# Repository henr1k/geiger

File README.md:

# geiger

Simple Geiger counter

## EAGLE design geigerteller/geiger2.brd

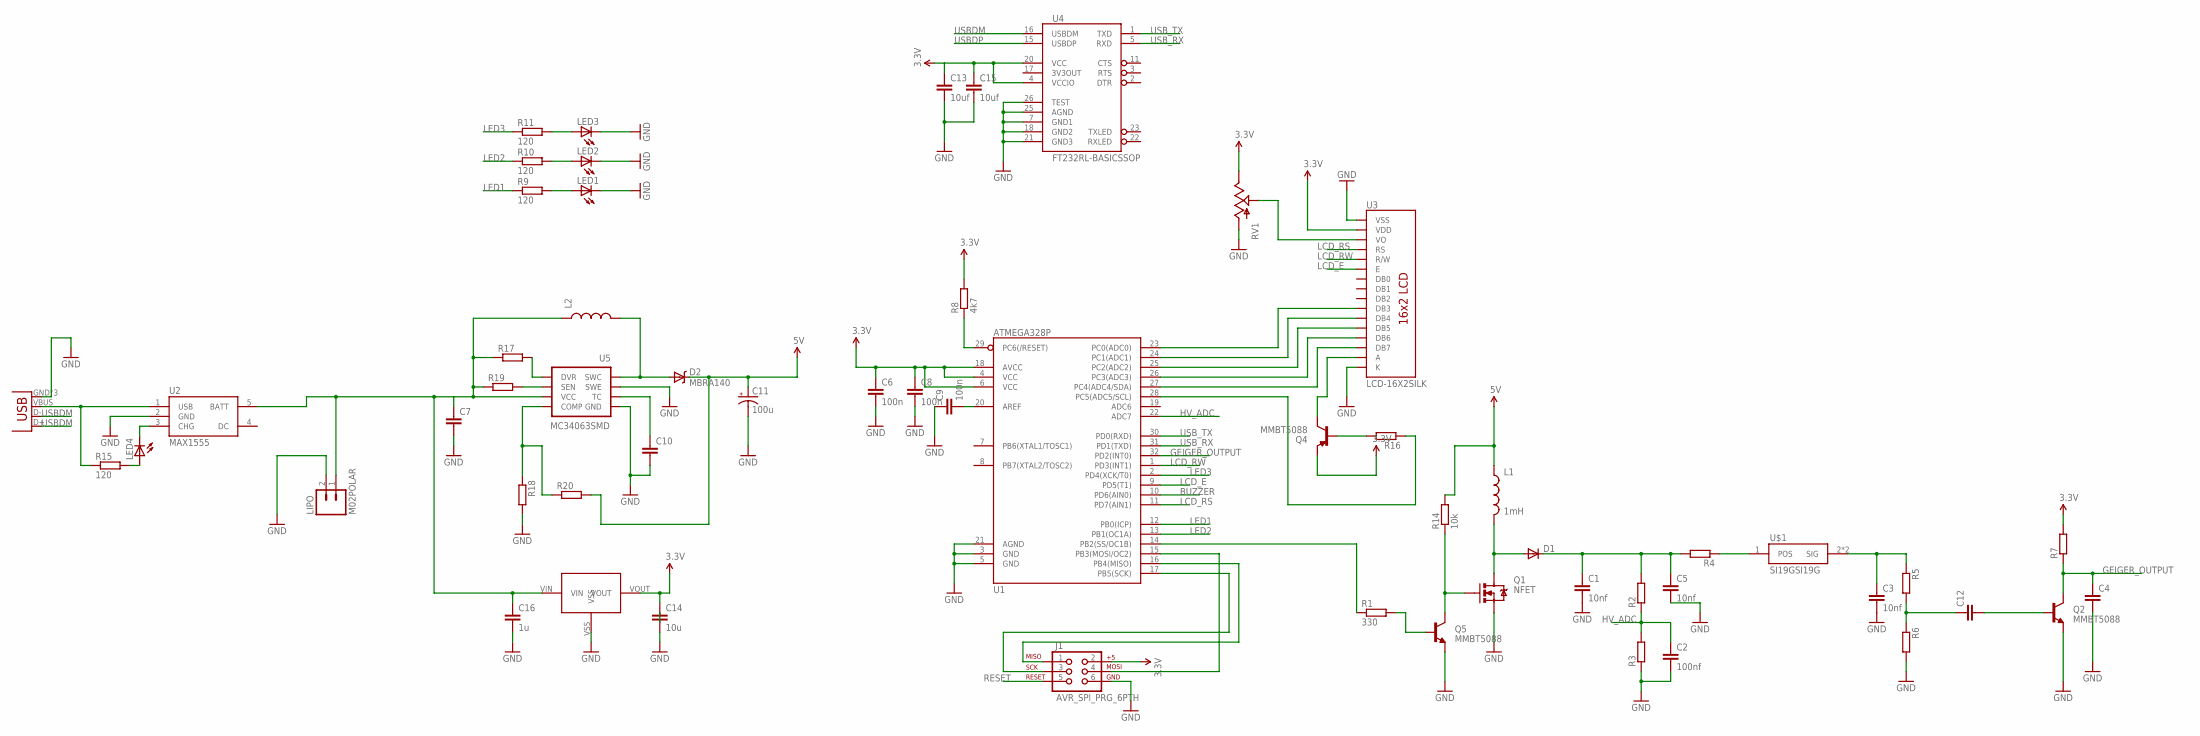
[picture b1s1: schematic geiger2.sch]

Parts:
C1, C3, C5: 10nf; C075-032X103
C2: 100nf; C0603
C4, C10, C12: C-EUC0603; C0603
C6, C8, C9: 100n; C0603
C7: C-EUC0805; C0805
C11: 100u; NIPPON_F80
C13, C15: 10uf; C0603
C14: 10u; C0603
C16: 1u; C0603
D1: DIODEPTH; DIODE-1N4001
D2: MBRA140; SMA-DIODE
J1: AVR_SPI_PRG_6PTH; 2X3
JP2: USB-MICROB
L1: 1mH; RLB0912
L2: INDUCTORCR75_V2; CR75_V2
LED1, LED2, LED3, LED4: LED0603; LED-0603
LIPO: M02POLAR; MOLEX-1X2
Q1: NFET; DPAK
Q2, Q5: MMBT5088; SOT23
Q4: MMBT5088; SOT23-3
R1: 330; R0603
R2, R3, R4, R5, R6: R-EU_0207/10; 0207/10
R7, R16, R17, R18, R19, R20: R-EU_R0603; R0603
R8: 4k7; R0603
R9, R10, R11, R15: 120; R0603
R14: 10k; R0603
RV1: POT100K_3362U; 3362U
U1: ATMEGA328P; TQFP32-08
U2: MAX1555; SOT23-5
U3: LCD-16X2SILK; LCD-16X2
U4: FT232RL-BASICSSOP; SSOP28DB
U5: MC34063SMD; SO08
U$1: SI19GSI19G; SI19G
U$2: XC6026; SOT23

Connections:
3.3V: C6.1, C8.1, C13.1, C14.1, C15.1, J1.2, Q4.2 (E), R7.2, R8.2, RV1.P$1 (E), U1.4 (VCC), U1.6 (VCC), U1.18 (AVCC), U3.2 (VDD), U4.4 (VCCIO), U4.20 (VCC), U$2.VOUT
6V: C7.1, C16.1, L2.P$1 (1), LIPO.1, R17.1, R19.1, U2.5 (BATT), U5.6 (VCC), U$2.VIN
12V: C11.+, D2.C, L1.1, R14.2, R20.2
BUZZER: U1.10 (PD6(AIN0))
GEIGER_OUTPUT: C4.1, Q2.3 (C), R7.1, U1.32 (PD2(INT0))
GND: C1.2, C2.2, C3.2, C4.2, C5.2, C6.2, C7.2, C8.2, C9.1, C10.2, C11.-, C13.2, C14.2, C15.2, C16.2, J1.6, JP2.GND, JP2.MT1 (GND), JP2.MT2 (GND), LED1.C, LED2.C, LED3.C, LIPO.2, Q1.3 (S), Q2.2 (E), Q5.2 (E), R3.1, R6.2, R18.2, RV1.P$3 (A), U1.3 (GND), U1.5 (GND), U1.21 (AGND), U2.2 (GND), U3.1 (VSS), U3.16 (K), U4.7 (GND1), U4.18 (GND2), U4.21 (GND3), U4.25 (AGND), U4.26 (TEST), U5.2 (SWE), U5.4 (GND), U$2.VSS
HV_ADC: C2.1, R2.1, R3.2, U1.22 (ADC7)
LCD_E: U1.9 (PD5(T1)), U3.6 (E)
LCD_RS: U1.11 (PD7(AIN1)), U3.4 (RS)
LCD_RW: U1.1 (PD3(INT1)), U3.5 (R/W)
LED1: R9.1, U1.12 (PB0(ICP))
LED2: R10.1, U1.13 (PB1(OC1A))
LED3: R11.1, U1.2 (PD4(XCK/T0))
unnamed: D1.A, L1.2, Q1.4 (D)
unnamed: R1.1, U1.14 (PB2(SS/OC1B))
unnamed: J1.1, U1.16 (PB4(MISO))
unnamed: Q5.1 (B), R1.2
unnamed: J1.3, U1.17 (PB5(SCK))
unnamed: J1.4, U1.15 (PB3(MOSI/OC2))
unnamed: C1.1, C5.1, D1.C, R2.2, R4.2
unnamed: R4.1, U$1.1 (POS)
unnamed: C3.1, R5.1, U$1.2 (SIG), U$1.3 (SIG)
unnamed: C12.1, R5.2, R6.1
unnamed: U1.23 (PC0(ADC0)), U3.10 (DB3)
unnamed: C9.2, U1.20 (AREF)
unnamed: U1.24 (PC1(ADC1)), U3.11 (DB4)
unnamed: U1.25 (PC2(ADC2)), U3.12 (DB5)
unnamed: U1.26 (PC3(ADC3)), U3.13 (DB6)
unnamed: U1.27 (PC4(ADC4/SDA)), U3.14 (DB7)
unnamed: D2.A, L2.P$2 (2), U5.1 (SWC)
unnamed: RV1.P$2 (S), U3.3 (VO)
unnamed: LED1.A, R9.2
unnamed: LED2.A, R10.2
unnamed: LED3.A, R11.2
unnamed: R18.1, R20.1, U5.5 (COMP)
unnamed: C12.2, Q2.1 (B)
unnamed: Q1.1 (G), Q5.3 (C), R14.1
unnamed: Q4.1 (B), R16.2
unnamed: C10.1, U5.3 (TC)
unnamed: LED4.A, R15.2
unnamed: Q4.3 (C), U3.15 (A)
unnamed: R16.1, U1.28 (PC5(ADC5/SCL))
unnamed: R17.2, U5.8 (DVR)
unnamed: R19.2, U5.7 (SEN)
unnamed: LED4.C, U2.3 (CHG)
unnamed: JP2.VBUS, R15.1, U2.1 (USB)
RESET: J1.5, R8.1, U1.29 (PC6(/RESET))
USBDM: JP2.D-, U4.16 (USBDM)
USBDP: JP2.D+, U4.15 (USBDP)
USB_RX: U1.31 (PD1(TXD)), U4.5 (RXD)
USB_TX: U1.30 (PD0(RXD)), U4.1 (TXD)

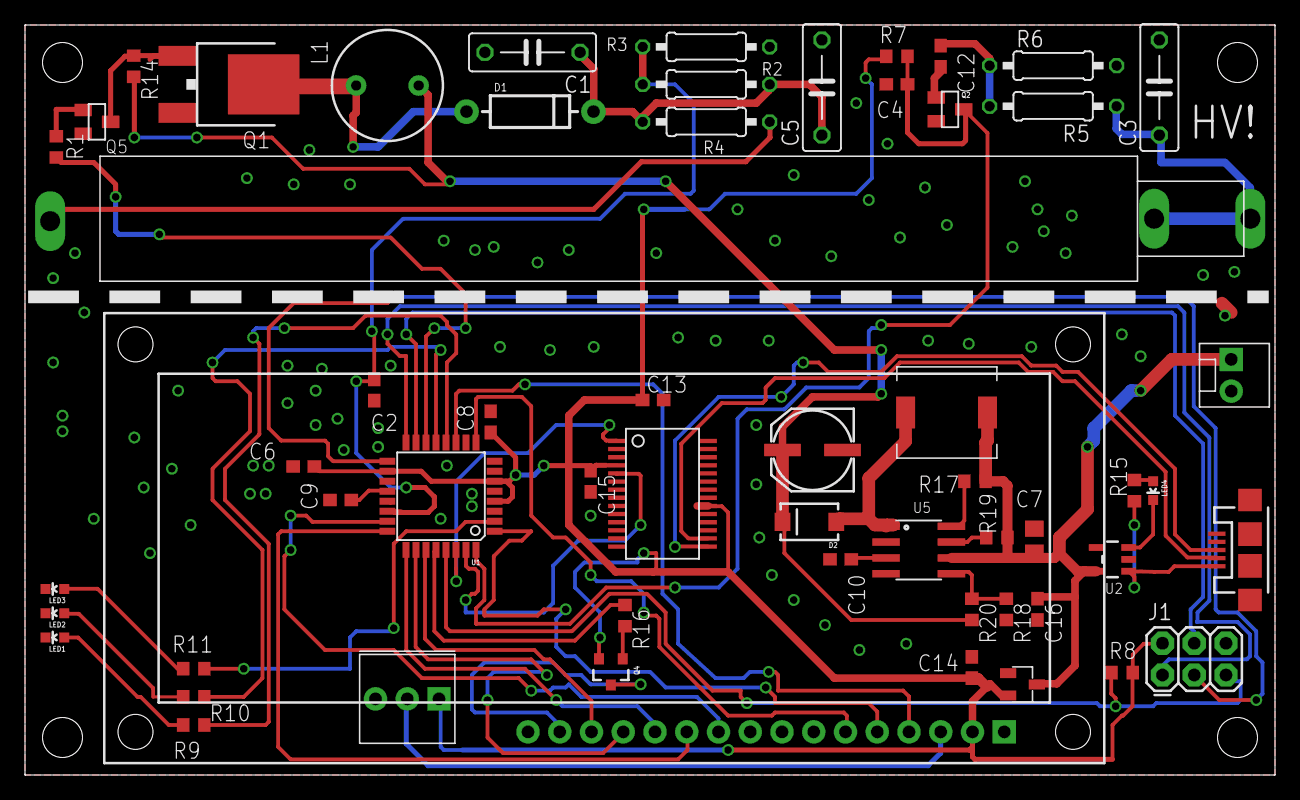
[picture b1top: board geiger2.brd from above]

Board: 2 copper layers, 100.0 x 60.0 mm, 57 parts (0 on the bottom side), 50 nets.

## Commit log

2016-02-15 added firmware
2016-02-15 Moved drill holes and Q5
2016-02-16 testing commit
2016-02-16 Added C7, moved battery connector

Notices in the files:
parts and their libraries:
SparkFun-Capacitors: Licensing: CC v3.0 Share-Alike You are welcome to use this library for commercial purposes.
